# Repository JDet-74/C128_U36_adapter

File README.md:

# C128_U36_adapter
A new design of the megabit adapter for U36 in the C128
 <br>
 <br>

# The story began ...
I tried to recreate the original Megabit adapter for the U36 socket in the C128.
The information to this project I found on cmb8bit.com. You can find the PDFs and the ROM binary file in the <strong>cmb8bit.com</strong> directory.

<ul>
    <li> <a href="./cbm8bit.com/Megabit_internal_rom_manual.pdf"> Megabit internal ROM manual</a> </li>
    <li> <a href="./cbm8bit.com/MegaBit-faq-howtoo.pdf"> Megabit FAQ HowTo</a> </li>
    <li> <a href="./cbm8bit.com/megabit-help.BIN"> megabit-help.bin</a> </li>
</ul>

# The issue was ...
I designed a PCB with the information of the PDFs and tested the soldered PCB. <br>
Unfortunately it does not work :( <br>
Thankfully a guy (Kinzi) from the great Forum64 helped me out by troubleshooting. <br>
I scoped the signals and figured out, that the transistor I used was too slow to trigger the D-FF. <br>
After that I tried logic gates - but this does not work either.
I figured out that there is a GLITCH on Pin12 of U3 <br>
 <br>
The GLITCH triggered always the D-FF and so it does not work :( what a bummer ;(

# The solution was ...
Kinzi mentioned that the /CS signal from pin12 of U3 has to be synchronized with the 1MHz clock of the C128. <br>
So I poked around with this variation and that was the success. <br>
The solution is to use two 74HCT173 D-FF and one 74HCT14 INV - so the /CS signal from pin 12 of U3 gets synchronized with the system clock
and addresses the ROM. BINGO <br>
<p>Take a look into the <a href="C128_U36_adapter_MANUAL.pdf"> C128 U36 adapter manual</a> or into the 
    <a href="Schematic_U36_adapter.pdf"> SCHEMATIC </a>for further information.</p>

# In the C128D-CR ...
 <br>

# In the C128 ...
 <br>

# Fabrication files
You can find a panelized GERBER file version and a single file version. <br>
The panelized version should work for the most PCB manufacturer.
I ordered by JLCPCB.

# Contact
For any questions (technical / experience), please use the issue tracking system of github.

Greetz 

JDet

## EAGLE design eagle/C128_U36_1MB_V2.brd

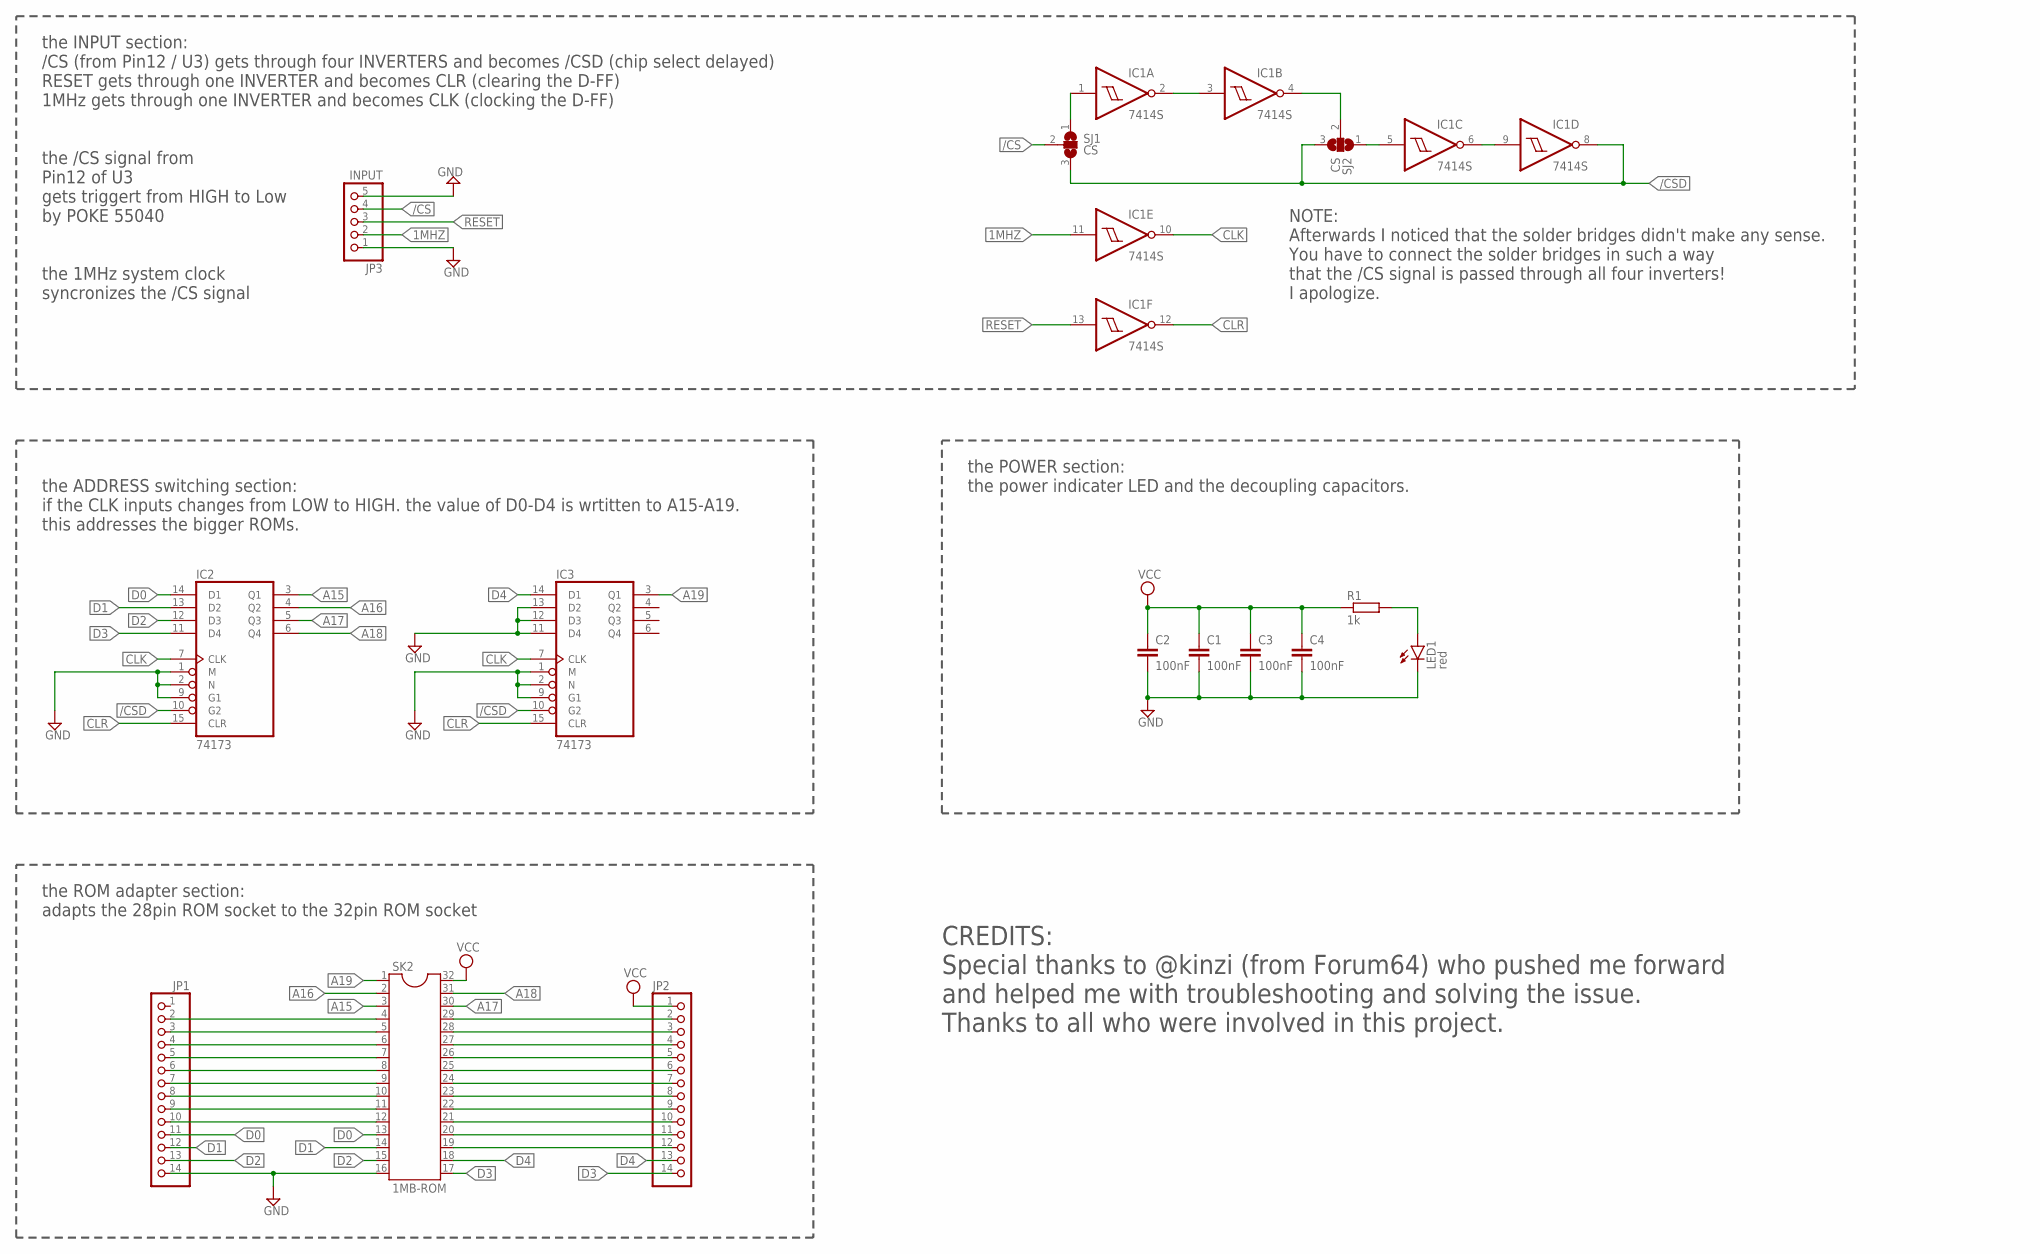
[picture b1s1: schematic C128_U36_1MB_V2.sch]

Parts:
C1, C2, C3, C4: 100nF; C0603K
IC1: 7414S; SO14_DET
IC2, IC3: 74173; SO16_DET
JP1, JP2: PINHD-1X14; 1X14
JP3: INPUT; 1X05/90
LED1: red; CHIPLED_0603
R1: 1k; R0603
SJ1, SJ2: CS; SJ_2
SK2: 1MB-ROM; DIL32

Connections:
1MHZ: IC1.11 (I), JP3.2
/CS: JP3.4, SJ1.2
/CSD: IC1.8 (O), IC2.10 (G2), IC3.10 (G2), SJ1.3, SJ2.3
A15: IC2.3 (Q1), SK2.3
A16: IC2.4 (Q2), SK2.2
A17: IC2.5 (Q3), SK2.30
A18: IC2.6 (Q4), SK2.31
A19: IC3.3 (Q1), SK2.1
CLK: IC1.10 (O), IC2.7 (CLK), IC3.7 (CLK)
CLR: IC1.12 (O), IC2.15 (CLR), IC3.15 (CLR)
D0: IC2.14 (D1), JP1.11, SK2.13
D1: IC2.13 (D2), JP1.12, SK2.14
D2: IC2.12 (D3), JP1.13, SK2.15
D3: IC2.11 (D4), JP2.14, SK2.17
D4: IC3.14 (D1), JP2.13, SK2.18
GND: C1.2, C2.2, C3.2, C4.2, IC1.7 (GND), IC2.1 (M), IC2.2 (N), IC2.8 (GND), IC2.9 (G1), IC3.1 (M), IC3.2 (N), IC3.8 (GND), IC3.9 (G1), IC3.11 (D4), IC3.12 (D3), IC3.13 (D2), JP1.14, JP3.1, JP3.5, LED1.C, SK2.16
unnamed: IC1.1 (I), SJ1.1
unnamed: IC1.2 (O), IC1.3 (I)
unnamed: IC1.4 (O), SJ2.2
unnamed: LED1.A, R1.2
unnamed: IC1.5 (I), SJ2.1
unnamed: IC1.6 (O), IC1.9 (I)
unnamed: JP1.2, SK2.4
unnamed: JP1.3, SK2.5
unnamed: JP1.4, SK2.6
unnamed: JP1.5, SK2.7
unnamed: JP1.6, SK2.8
unnamed: JP1.7, SK2.9
unnamed: JP1.8, SK2.10
unnamed: JP1.9, SK2.11
unnamed: JP2.2, SK2.29
unnamed: JP2.3, SK2.28
unnamed: JP2.4, SK2.27
unnamed: JP2.5, SK2.26
unnamed: JP2.6, SK2.25
unnamed: JP2.7, SK2.24
unnamed: JP2.8, SK2.23
unnamed: JP2.9, SK2.22
unnamed: JP2.10, SK2.21
unnamed: JP2.11, SK2.20
unnamed: JP2.12, SK2.19
unnamed: JP1.10, SK2.12
RESET: IC1.13 (I), JP3.3
VCC: C1.1, C2.1, C3.1, C4.1, IC1.14 (VCC), IC2.16 (VCC), IC3.16 (VCC), JP2.1, R1.1, SK2.32

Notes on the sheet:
the 1MHz system clock syncronizes the /CS signal
the /CS signal from Pin12 of U3 gets triggert from HIGH to Low by POKE 55040
the INPUT section: /CS (from Pin12 / U3) gets through four INVERTERS and becomes /CSD (chip select delayed) RESET gets through one INVERTER and becomes CLR (clearing the D-FF) 1MHz gets through one INVERTER and becomes CLK (clocking the D-FF)
the ROM adapter section: adapts the 28pin ROM socket to the 32pin ROM socket
the ADDRESS switching section: if the CLK inputs changes from LOW to HIGH. the value of D0-D4 is wrtitten to A15-A19. this addresses the bigger ROMs.
the POWER section: the power indicater LED and the decoupling capacitors.
CREDITS: Special thanks to @kinzi (from Forum64) who pushed me forward and helped me with troubleshooting and solving the issue. Thanks to all who were involved in this project.
NOTE: Afterwards I noticed that the solder bridges didn't make any sense. You have to connect the solder bridges in such a way that the /CS signal is passed through all four inverters! I apologize.

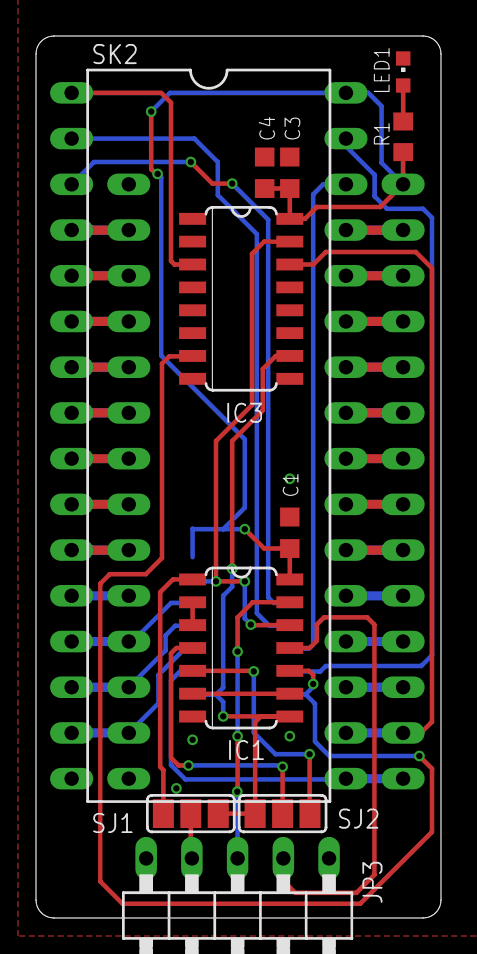
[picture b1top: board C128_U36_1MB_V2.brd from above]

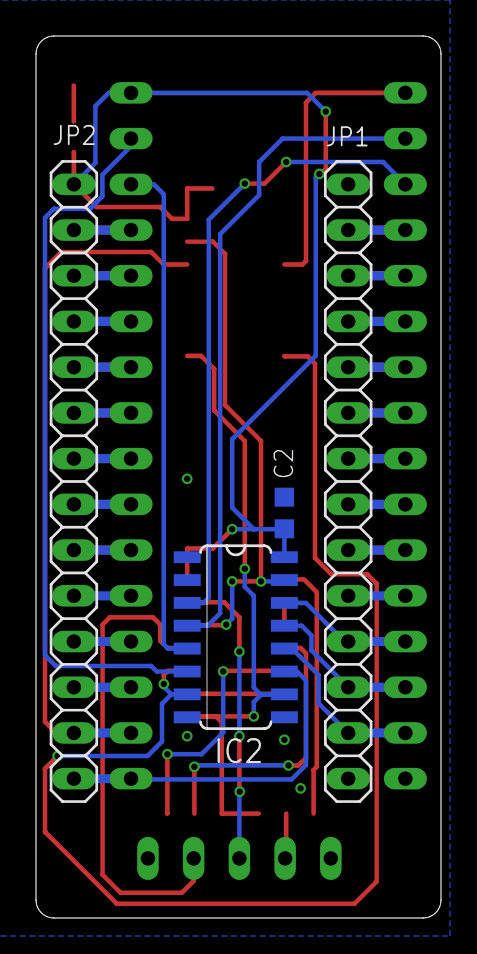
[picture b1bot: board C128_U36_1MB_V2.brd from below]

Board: 2 copper layers, 22.5 x 49.0 mm, 15 parts (4 on the bottom side), 44 nets.

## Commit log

2022-07-19 my eagle project files
    here are my ealge project files for everybody to use them ...
